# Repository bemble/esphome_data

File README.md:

# esphome-data

> My ESPHome data.

- **garage-door:** enable the control of my front garage door 
- **gazpar:** get gaz consumption with french gaz meter "gazpar" (details [here, in french](./ressources/gazpar.md))
- **station-meteo:** `WIP` meteo station

## Fix secrets

In `common` folder, add a `secrets.yaml` file which starts with:

```yaml
<<: !include ../secrets.yaml
```

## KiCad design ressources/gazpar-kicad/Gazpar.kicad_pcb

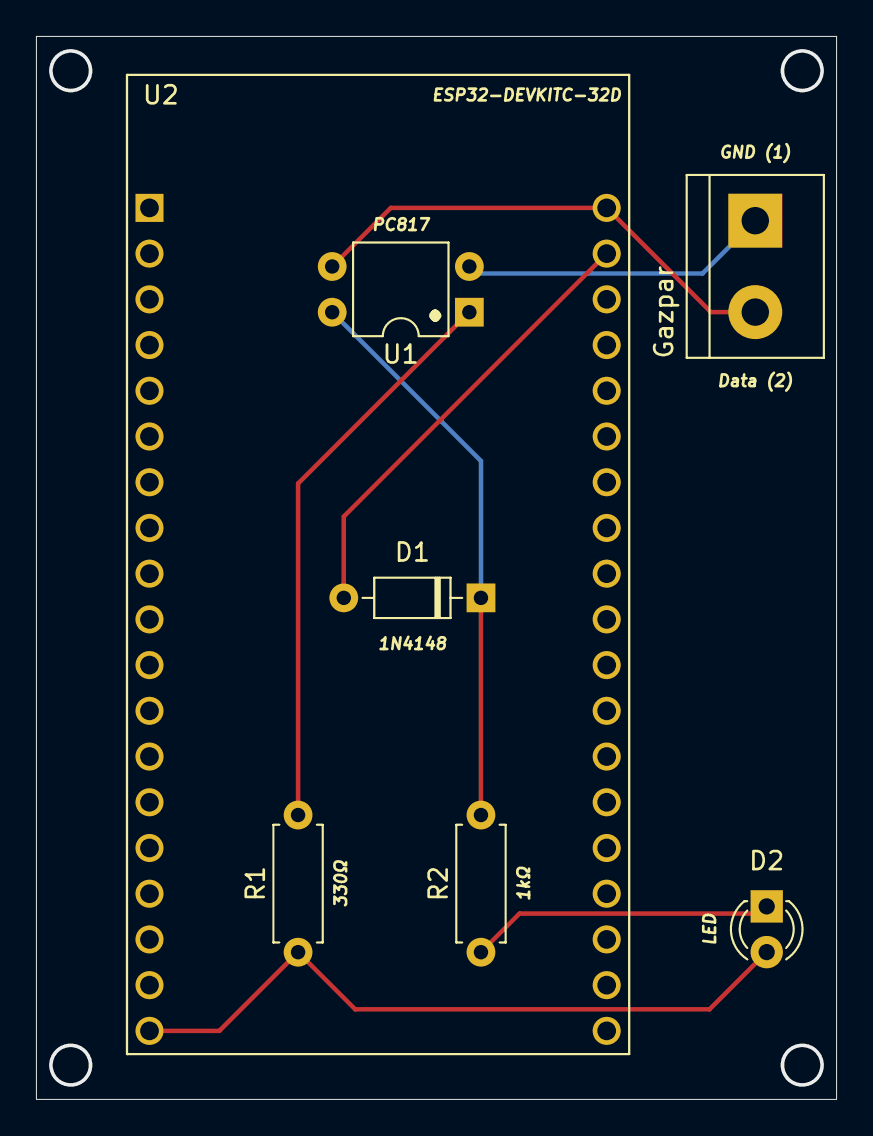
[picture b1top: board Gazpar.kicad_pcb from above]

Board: 2 copper layers, 44.4 x 59.1 mm, 7 parts (0 on the bottom side), 7 nets.

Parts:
D1: 1N4148; D_DO-35_SOD27_P7.62mm_Horizontal
D2: LED; LED_D3.0mm
Gazpar: G-; TerminalBlock_bornier-2_P5.08mm
R1: 330Ω; R_Axial_DIN0207_L6.3mm_D2.5mm_P7.62mm_Horizontal
R2: 1kΩ; R_Axial_DIN0207_L6.3mm_D2.5mm_P7.62mm_Horizontal
U1: PC817; DIP-4_W7.62mm
U2: ESP32-DEVKITC-32D; MODULE_ESP32-DEVKITC-32D

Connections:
unnamed: D1.1 (K), R2.2, U1.4
unnamed: D1.2 (A), U2.21 (IO23)
unnamed: D2.1 (K), R2.1
unnamed: D2.2 (A), R1.1, U2.19 (EXT_5V)
unnamed: Gazpar.1, U1.2
unnamed: Gazpar.2, U1.3, U2.20 (GND3)
unnamed: R1.2, U1.1

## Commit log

2022-05-08 feat: add gazpar and station-meteo
2022-05-08 feat(multiplexed_sht): make it a little bit more generic
2022-05-08 feat(sht): change the way to remove deviant values
2022-05-08 feat(weather): add rain meter
2022-05-14 feat(station-meteo): add wind direction
2022-05-14 fix(station-meteo): prevent wind direction sensors to be updated if no big change
2022-05-14 doc(davis): add hardware info
2022-06-10 feat(gazpar): update gazpar and add instructions
2022-06-10 doc: remove previsou image
2022-06-26 doc(gazpar): move from esp01 to esp32
2022-06-26 doc(gazpar): add link to kicad file for esp32
2022-09-20 use packages for common stuff and update files
2022-12-15 fix: remove bluetooth proxy
